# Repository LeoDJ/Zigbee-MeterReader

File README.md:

# nRF52840 Zigbee Power Meter

**WIP!** Note: This project is currently under heavy development and should not be used in its current state.

### [Software Documentation](Software)

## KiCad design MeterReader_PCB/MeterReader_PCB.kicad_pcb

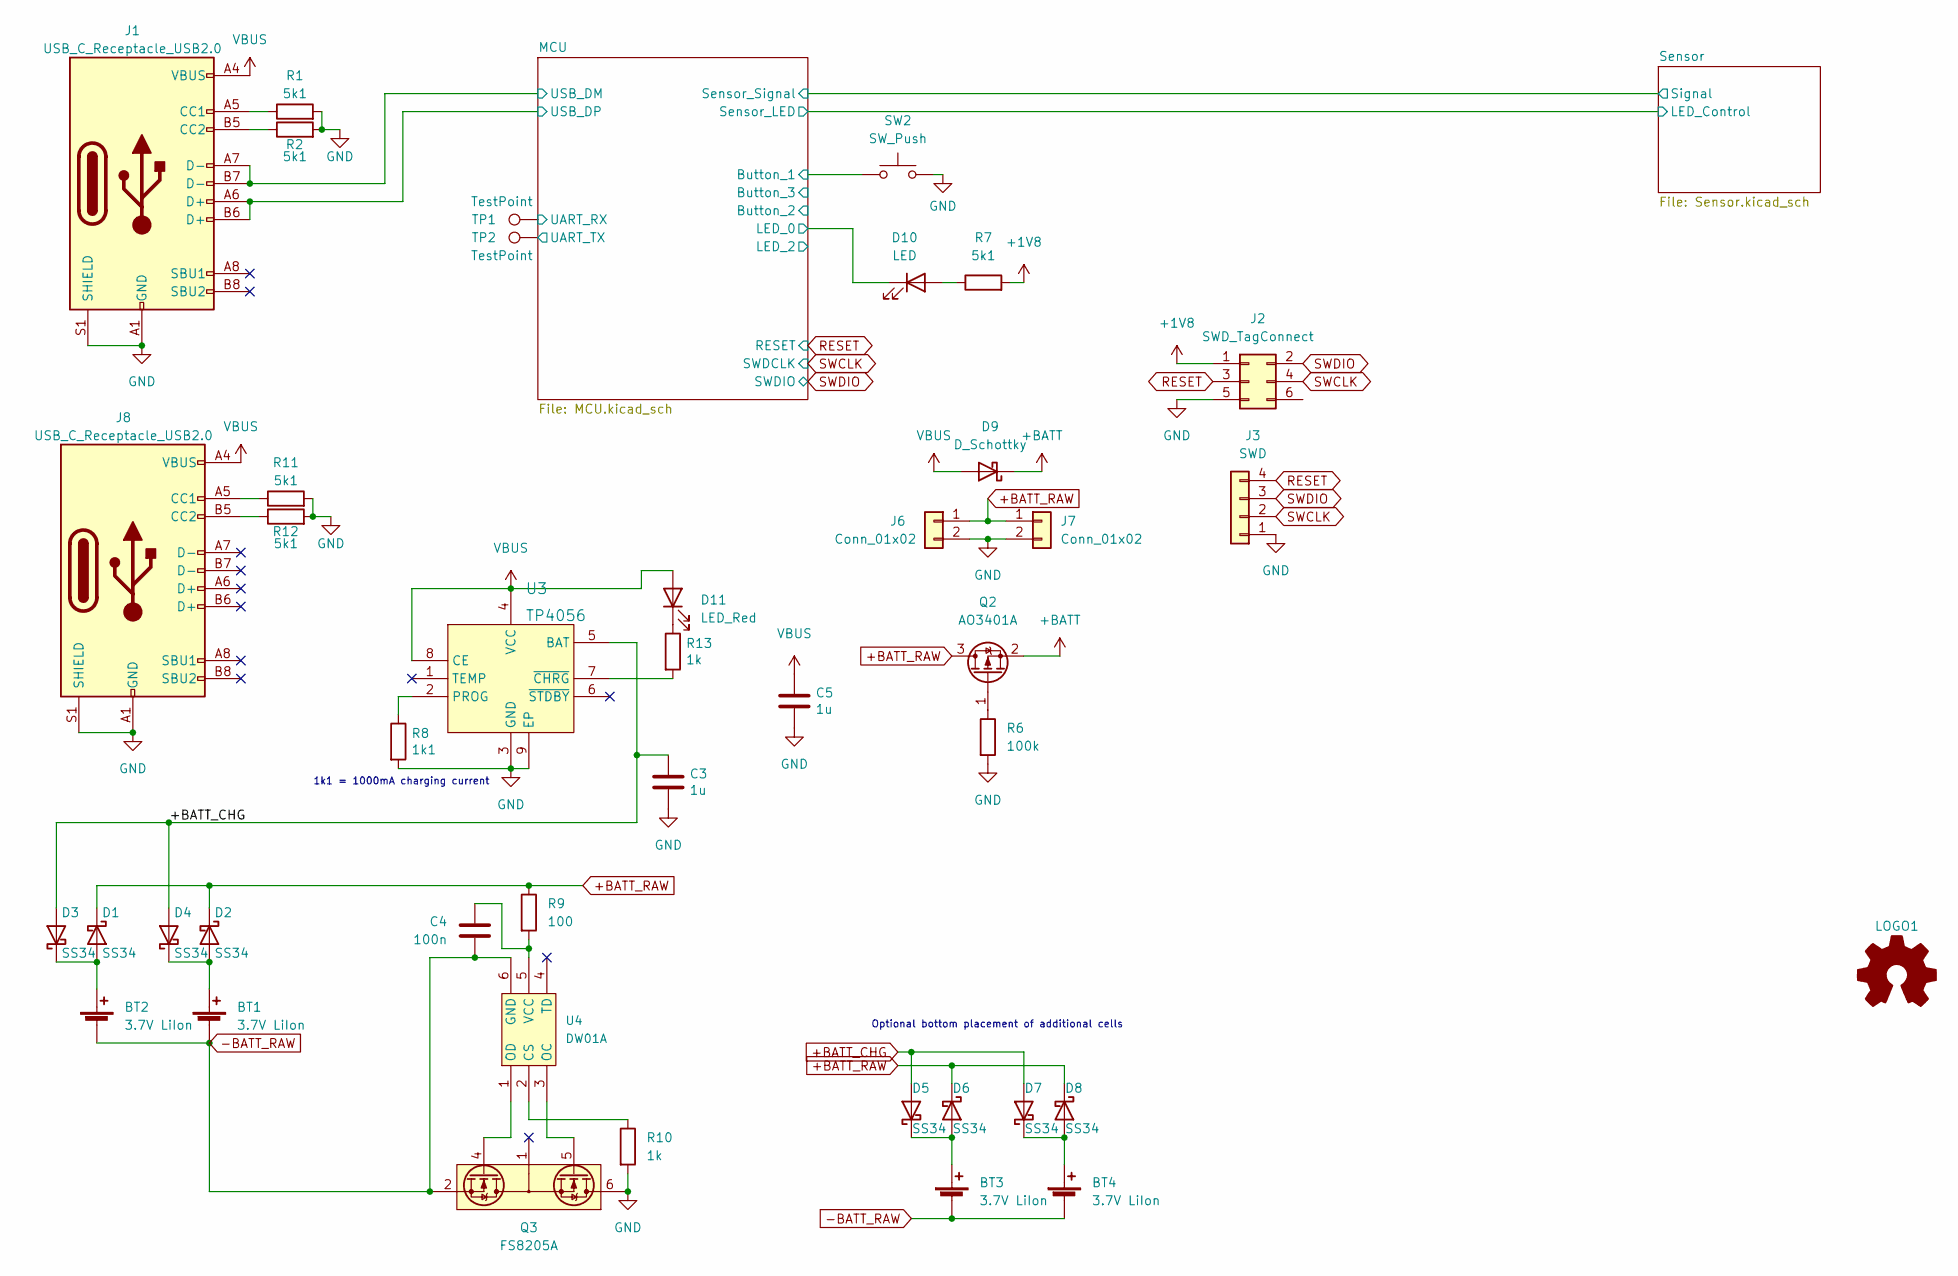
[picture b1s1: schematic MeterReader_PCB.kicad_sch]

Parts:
BT1, BT2, BT3, BT4: 3.7V LiIon; BatteryHolder_Keystone_1042_1x18650
C3, C5: 1u; C_0603_1608Metric
C4: 100n; C_0603_1608Metric
D1, D2, D3, D4, D5, D6, D7, D8: SS34; D_SMA
D9: D_Schottky; D_SOD-323
D10: LED; LED_0603_1608Metric
D11: LED_Red; LED_0603_1608Metric
J1, J8: USB_C_Receptacle_USB2.0; USB_C_Receptacle_HRO_TYPE-C-31-M-12
J2: SWD_TagConnect; Paw-Connect_TC2030-IDC-NL_2x03_P1.27mm_Vertical
J3: SWD; PinHeader_1x04_P2.54mm_Vertical
J6, J7: Conn_01x02; JST_PH_S2B-PH-K_1x02_P2.00mm_Horizontal
LOGO1: Logo_Open_Hardware_Small; OSHW-Symbol_6.7x6mm_SilkScreen
Q2: AO3401A; SOT-23
Q3: FS8205A; TSSOP-8_4.4x3mm_P0.65mm
R1, R2, R7, R11, R12: 5k1; R_0603_1608Metric
R6: 100k; R_0603_1608Metric
R8: 1k1; R_0603_1608Metric
R9: 100; C_0603_1608Metric
R10: 1k; C_0603_1608Metric
R13: 1k; R_0603_1608Metric
SW2: SW_Push; SW_SPST_TL3342
TP1, TP2: TestPoint; TestPoint_Pad_1.5x1.5mm
U3: TP4056; SOIC-8-1EP_3.9x4.9mm_P1.27mm_EP2.41x3.3mm_ThermalVias
U4: DW01A; SOT-23-6

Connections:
+1V8: J2.1, R7.2; also elsewhere on the board
+BATT: D9.1 (K), Q2.2 (S); also elsewhere on the board
+BATT_CHG: C3.1, D3.2 (A), D4.2 (A), D5.2 (A), D7.2 (A), U3.5 (BAT)
+BATT_RAW: D1.1 (K), D2.1 (K), D6.1 (K), D8.1 (K), J6.1, J7.1, Q2.3 (D), R9.1
-BATT_RAW: BT1.2 (-), BT2.2 (-), BT3.2 (-), BT4.2 (-), C4.1, Q3.2 (S1), U4.6 (GND)
/MCU/Button_1: SW2.1; also elsewhere on the board
/MCU/LED_0: D10.1 (K); also elsewhere on the board
/MCU/UART_RX: TP1.1; also elsewhere on the board
/MCU/UART_TX: TP2.1; also elsewhere on the board
/MCU/USB_DM: J1.A7 (D-), J1.B7 (D-); also elsewhere on the board
/MCU/USB_DP: J1.A6 (D+), J1.B6 (D+); also elsewhere on the board
GND: C3.2, C5.2, J1.A1 (GND), J1.A12 (GND), J1.B1 (GND), J1.B12 (GND), J1.S1 (SHIELD), J2.5, J3.1, J6.2, J7.2, J8.A1 (GND), J8.A12 (GND), J8.B1 (GND), J8.B12 (GND), J8.S1 (SHIELD), Q3.6 (S2), R1.2, R2.2, R6.2, R8.2, R10.2, R11.2, R12.2, SW2.2, U3.3 (GND), U3.9 (EP); also elsewhere on the board
unnamed: BT1.1 (+), D2.2 (A), D4.1 (K)
unnamed: BT2.1 (+), D1.2 (A), D3.1 (K)
unnamed: BT3.1 (+), D5.1 (K), D6.2 (A)
unnamed: BT4.1 (+), D7.1 (K), D8.2 (A)
unnamed: C4.2, R9.2, U4.5 (VCC)
unnamed: D10.2 (A), R7.1
unnamed: D11.1 (K), R13.1
unnamed: J1.A5 (CC1), R1.1
unnamed: J1.B5 (CC2), R2.1
unnamed: J8.A5 (CC1), R11.1
unnamed: J8.B5 (CC2), R12.1
unnamed: Q2.1 (G), R6.1
unnamed: Q3.4 (G1), U4.1 (OD)
unnamed: Q3.5 (G2), U4.3 (OC)
unnamed: R8.1, U3.2 (PROG)
unnamed: R10.1, U4.2 (CS)
unnamed: R13.2, U3.7 (~CHRG)
RESET: J2.3, J3.4; also elsewhere on the board
SWCLK: J2.4, J3.2; also elsewhere on the board
SWDIO: J2.2, J3.3; also elsewhere on the board
VBUS: C5.1, D9.2 (A), D11.2 (A), J1.A4 (VBUS), J1.A9 (VBUS), J1.B4 (VBUS), J1.B9 (VBUS), J8.A4 (VBUS), J8.A9 (VBUS), J8.B4 (VBUS), J8.B9 (VBUS), U3.4 (VCC), U3.8 (CE); also elsewhere on the board

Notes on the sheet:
1k1 = 1000mA charging current
Optional bottom placement of additional cells

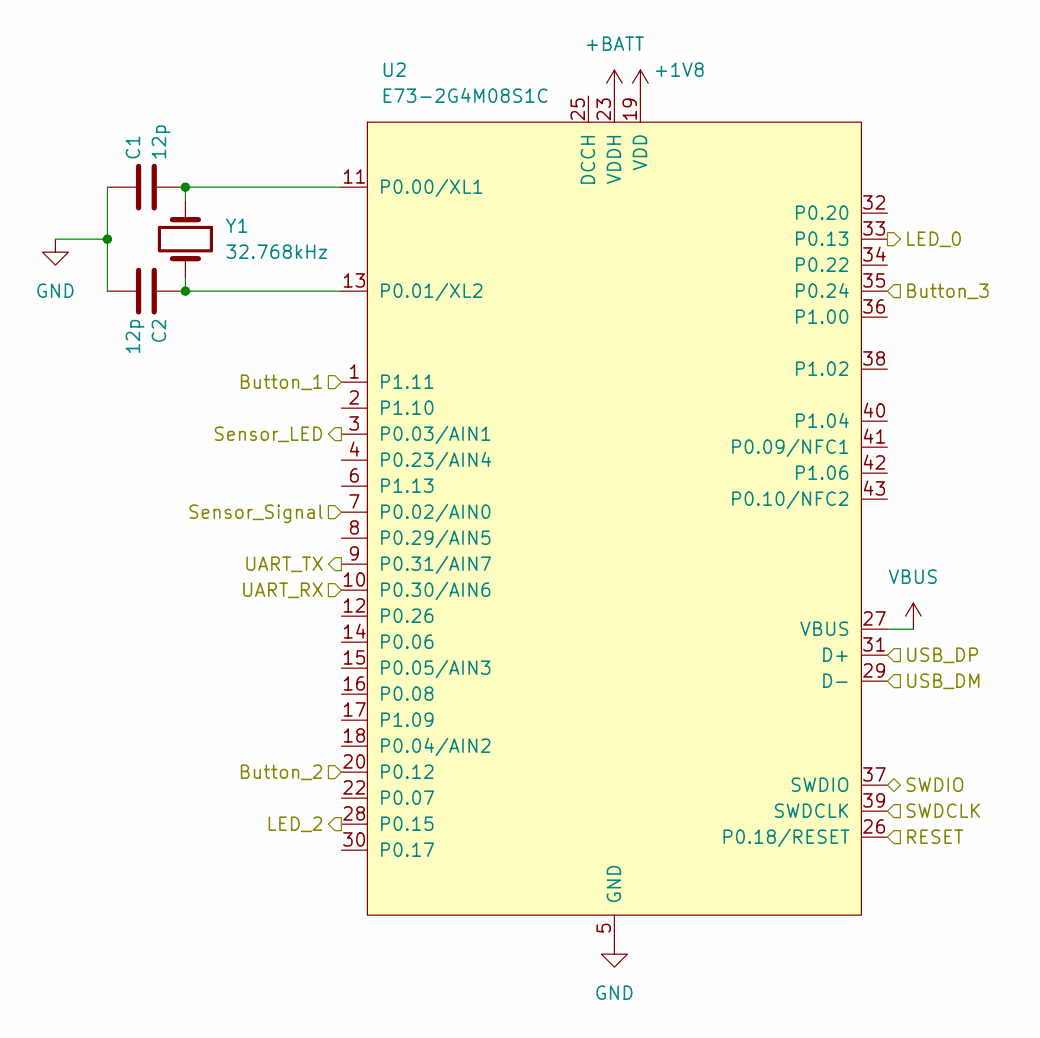
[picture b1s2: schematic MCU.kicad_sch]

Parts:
C1, C2: 12p; C_0603_1608Metric
U2: E73-2G4M08S1C
Y1: 32.768kHz; Crystal_SMD_3215-2Pin_3.2x1.5mm

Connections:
+1V8: U2.19 (VDD); also elsewhere on the board
+BATT: U2.23 (VDDH); also elsewhere on the board
/MCU/Button_1: U2.1 (P1.11); also elsewhere on the board
/MCU/Button_2: U2.20 (P0.12)
/MCU/Button_3: U2.35 (P0.24)
/MCU/LED_0: U2.33 (P0.13); also elsewhere on the board
/MCU/LED_2: U2.28 (P0.15)
/MCU/Sensor_LED: U2.3 (P0.03/AIN1); also elsewhere on the board
/MCU/Sensor_Signal: U2.7 (P0.02/AIN0); also elsewhere on the board
/MCU/UART_RX: U2.10 (P0.30/AIN6); also elsewhere on the board
/MCU/UART_TX: U2.9 (P0.31/AIN7); also elsewhere on the board
/MCU/USB_DM: U2.29 (D-); also elsewhere on the board
/MCU/USB_DP: U2.31 (D+); also elsewhere on the board
GND: C1.1, C2.2, U2.5 (GND), U2.21 (GND), U2.24 (GND); also elsewhere on the board
unnamed: C1.2, U2.11 (P0.00/XL1), Y1.1
unnamed: C2.1, U2.13 (P0.01/XL2), Y1.2
RESET: U2.26 (P0.18/RESET); also elsewhere on the board
SWCLK: U2.39 (SWDCLK); also elsewhere on the board
SWDIO: U2.37 (SWDIO); also elsewhere on the board
VBUS: U2.27 (VBUS); also elsewhere on the board

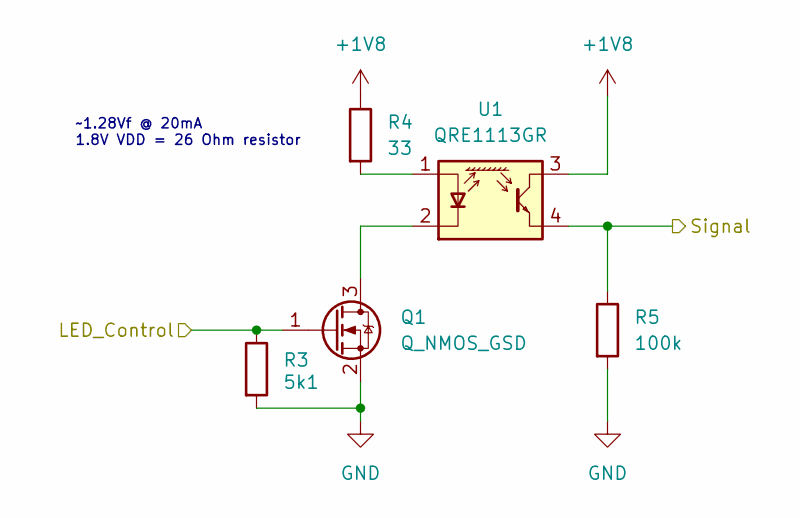
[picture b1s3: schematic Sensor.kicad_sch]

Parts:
Q1: Q_NMOS_GSD; SOT-23
R3: 5k1; R_0603_1608Metric
R4: 33; R_0603_1608Metric
R5: 100k; R_0603_1608Metric
U1: QRE1113GR; OnSemi_CASE100CY

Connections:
+1V8: R4.1, U1.3; also elsewhere on the board
/MCU/Sensor_LED: Q1.1 (G), R3.1; also elsewhere on the board
/MCU/Sensor_Signal: R5.1, U1.4; also elsewhere on the board
GND: Q1.2 (S), R3.2, R5.2; also elsewhere on the board
unnamed: Q1.3 (D), U1.2 (K)
unnamed: R4.2, U1.1 (A)

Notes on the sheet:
~1.28Vf @ 20mA 1.8V VDD = 26 Ohm resistor

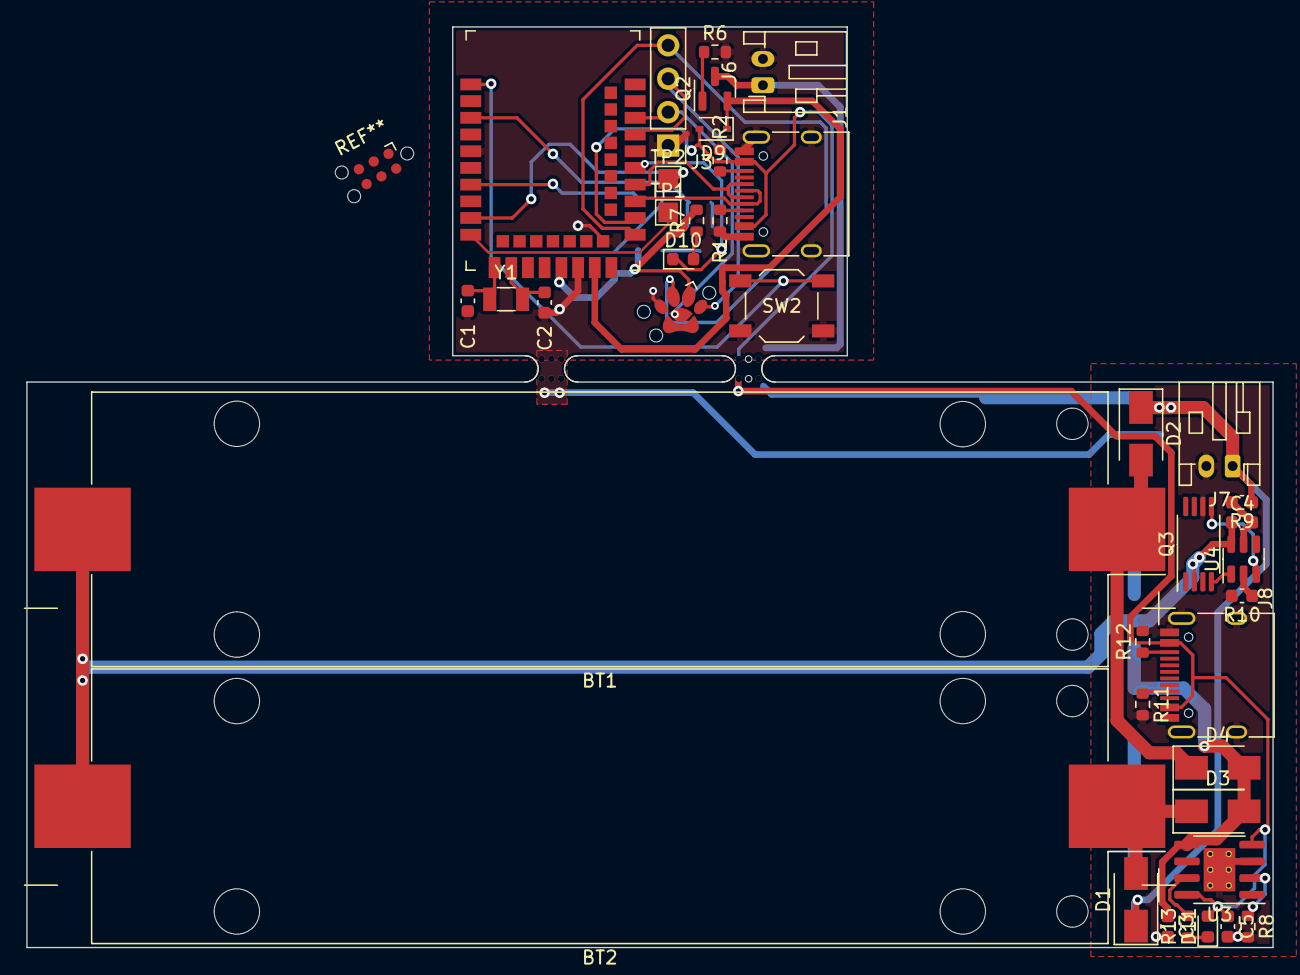
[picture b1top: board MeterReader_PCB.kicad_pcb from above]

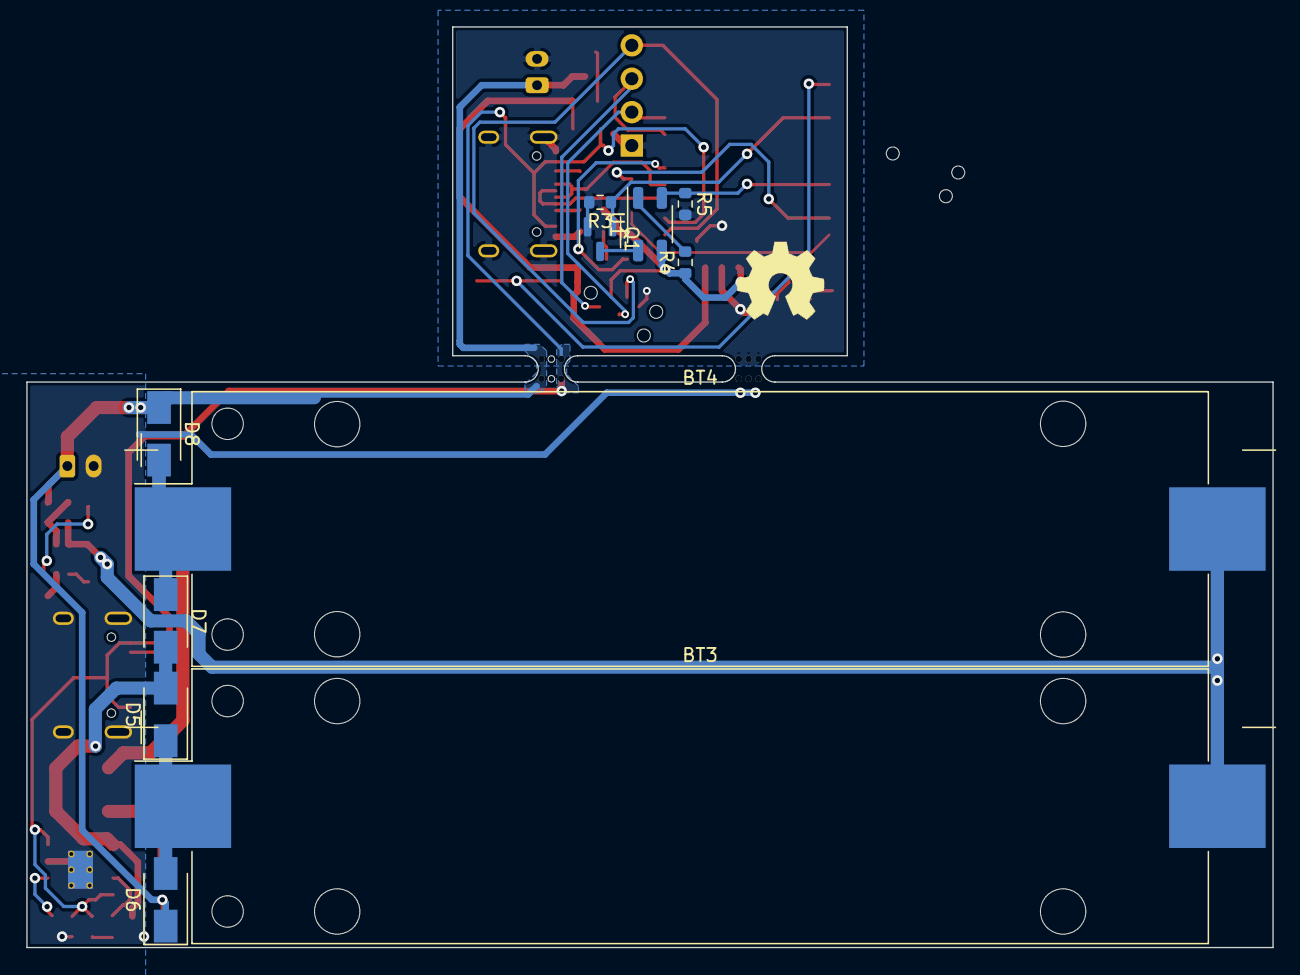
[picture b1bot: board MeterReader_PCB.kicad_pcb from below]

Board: 2 copper layers, 94.8 x 70.0 mm, 53 parts (12 on the bottom side), 39 nets.

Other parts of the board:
mouse-bite-2mm-slot, mouse-bite-2mm-slot#2: VAL**; mouse-bite-2mm-slot

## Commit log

2021-03-11 got a basic example running
2021-03-11 add LICENSE
2021-03-12 zigbee2mqtt battery state reporting working
2021-03-12 begin implementing metering cluster
2021-03-13 metering cluster working
2021-03-14 Try to make meter reading writeable
    But zigbee2mqtt always sends out 0, although toSend is correct.
    Maybe the Zigbee stack on the stick really doesn't like writing to read only attributes?
2021-03-14 Writing meter reading works
2021-03-15 Implement setting meter reading factor
2021-03-18 implement rudimentary ADC read
    ToDo: check if value is correct and actually corresponds to VDDH
2021-03-18 add CPU temperature measurement
2021-03-19 crude implementation of battery state reporting
2021-03-22 restructure ADC before adding phototransistor input
2021-03-27 begin implementing IR sensor reading
    ADC reading currently doesn't get triggered the second time.
    To investigate tomorrow tho.
2021-03-27 fixed second ADC sampling
2021-03-28 IR sensor readings now working
2021-05-27 implement basic IR sensor pulse detection
2021-05-27 add PDFs
2021-09-29 begin PCB layout
2022-10-06 move active components onto sensor PCB, finish layout of sensor PCB
2022-10-06 add VBUS diode and trace to MCU
2022-10-06 finish layout of battery pack PCB
2022-10-08 finish track layout of battery module && merge both modules
